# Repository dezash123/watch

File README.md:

ecad / code for my custom smartwatch!!!!!

[MCAD](https://cad.onshape.com/documents/7a2f9e69e051d257ea5e1b33/)

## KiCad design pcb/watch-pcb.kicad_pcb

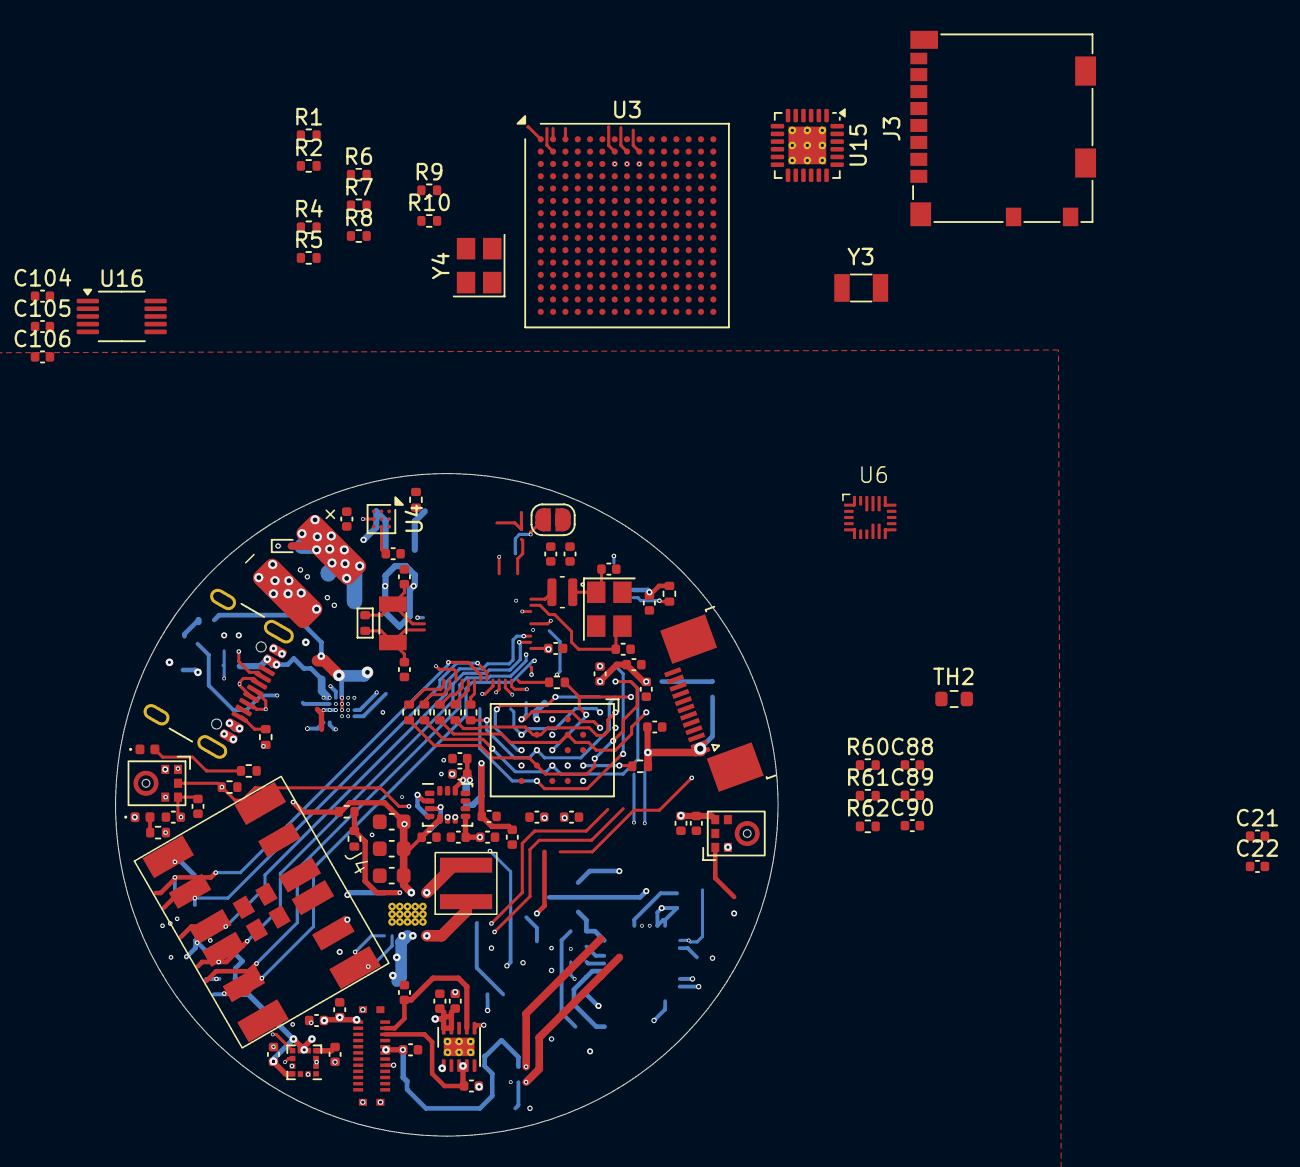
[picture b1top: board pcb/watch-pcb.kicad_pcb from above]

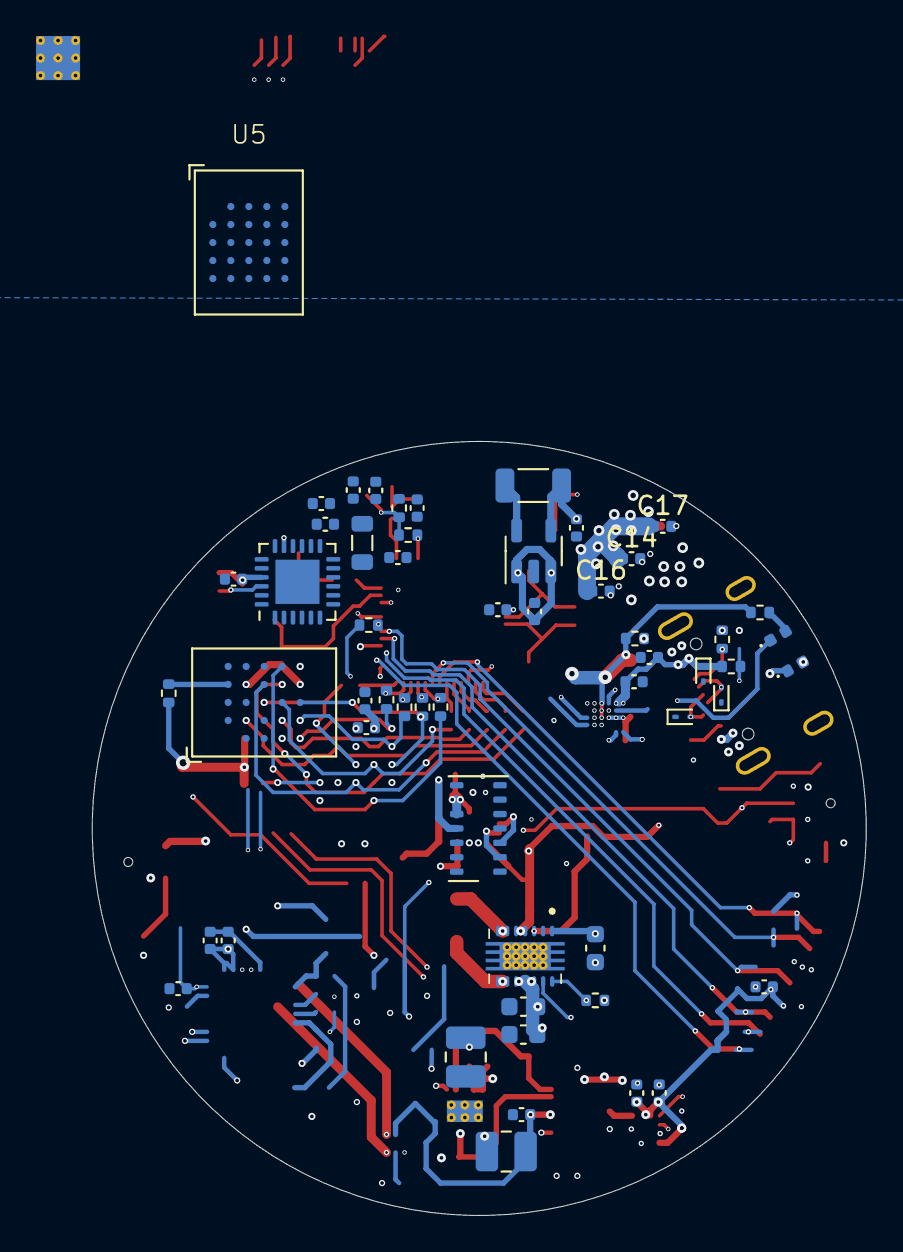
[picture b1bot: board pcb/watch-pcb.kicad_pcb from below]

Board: 6 copper layers, 43.0 x 43.0 mm, 158 parts (55 on the bottom side), 113 nets.

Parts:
BT1: Battery; Battery_Connector
C1, C2: 10uF; C_0603_1608Metric
C3, C58, C88: 4.7uF; C_0402_1005Metric
C4: 100nF; C_0603_1608Metric
C5, C36: 10nF; C_0402_1005Metric
C6, C13, C43, C44, C49, C52, C55, C62, C63, C89, C90: 10uF; C_0402_1005Metric
C7, C8, C10: 22uF; C_0603_1608Metric
C9, C11, C14, C18, C26, C31, C33, C40, C45, C47, C59, C64, C66, C69, C70, C75, C104, C106: 1uF; C_0402_1005Metric
C12, C17, C30, C32, C35, C38, C39, C46, C48, C50, C54, C57, C60, C61, C65, C67, C68, C71, C72, C73, C74, C76, C77, C78, C79, C105: 100nF; C_0402_1005Metric
C15: 2.2uF; C_0402_1005Metric
C16: 47nF; C_0402_1005Metric
C21, C22, C27, C28, C41, C42: C; C_0402_1005Metric
D1: STATUS1; LED_0402_1005Metric
D2, D3, D4, D5: ESD9B5.0ST5G; D_SOD-923
D6: CHARGING; LED_0402_1005Metric
D7: POWER GOOD; LED_0402_1005Metric
D15: STATUS0; LED_0402_1005Metric
J1: DAUGHTER; TE_1-1734839-2_1x12-1MP_P0.5mm_Horizontal
J2: USB_C_Receptacle; USB_C_Receptacle_GCT_USB4105-xx-A_16P_TopMnt_Horizontal
J3: Micro_SD_Card; microSD_HC_Molex_104031-0811
J4: ELV1411A
J6: TT143AMC12C; OK-14GF024-04
JP1: RESET=LOW; SolderJumper-2_P1.3mm_Open_RoundedPad1.0x1.5mm
L1: 1.5uH; XFL4020-152ME
L2: 1uH; L_1206_3216Metric
L5: 2nH; L_0805_2012Metric
L6: 24nH; L_Coilcraft_XFL2010
L7, L8: 10uH; L_1008_2520Metric
MK1, MK2: ICS-43434; InvenSense_ICS-43434-6_3.5x2.65mm
R1, R2, R4, R5, R6, R7, R8, R9, R10, R19, R31, R32, R40, R52, R53, R54: 10k; R_0402_1005Metric
R3, R39, R55, R56, R57: R; R_0402_1005Metric
R11, R12: 5.1k; R_0402_1005Metric
R13: 180k; R_0402_1005Metric
R14, R15: 1M; R_0402_1005Metric
R16: 22.1k; R_0402_1005Metric
R33: 499; R_0402_1005Metric
R34, R35, R36, R37, R38, R41, R42, R43, R44, R45: 0; R_0402_1005Metric
R60: 30.1; R_0402_1005Metric
R61: 5.32k; R_0402_1005Metric
R62: 5k; R_0402_1005Metric
TH2: 103AT-2 10k; R_0603_1608Metric
U1: ADP2108AUJ-1.8; TSOT-23-5
U2: TPS63021; Texas_VSON-14_3x4mm_ThermalPad
U3: STM32H7S7L8H6H; ST_TFBGA-225_13x13mm_Layout15x15_P0.8mm
U4: BQ27427YZFR; Texas_DSBGA-9_1.62mmx1.58mm_Layout3x3_P0.5mm
U5: APS256XXN-OBR-BG; BGA-24_6.0x8.0mm_Layout5x5_P1.0mm
U6: BQ25628E; Texas_WQFN-18_2.5x3.0mm_P0.4mm
U7: MX25LM51245GXDI00; BGA-24_6.0x8.0mm_Layout5x5_P1.0mm
U8: APS12808L-3OBMx; BGA-24_6.0x8.0mm_Layout5x5_P1.0mm
U9: TCA9535MRGER; VQFN-24-1EP_4x4mm_P0.5mm_EP2.45x2.45mm
U10: MAX30102; Maxim_OLGA-14_3.3x5.6mm_P0.8mm
U11: TPS65631W; WSON-10-1EP_2.5x2.5mm_P0.5mm_EP1.2x2mm_ThermalVias
U13: LSM6DSV16XTR; LGA-14_3x2.5mm_P0.5mm_LayoutBorder3x4y
U14: LIS3MDL; LGA-12_2x2mm_P0.5mm
U15: TXS02612RTW; WQFN-24-1EP_4x4mm_P0.5mm_EP2.45x2.45mm_ThermalVias
U16: DRV2605LDGS; VSSOP-10_3x3mm_P0.5mm
Y1, Y3: 32.768kHz; Crystal_SMD_3215-2Pin_3.2x1.5mm
Y2, Y4: 40MHz(10ppm); Crystal_SMD_3225-4Pin_3.2x2.5mm

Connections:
+1V8: C6.1, C54.2, C55.2, J1.3, J3.4 (VDD), L2.2, U1.4 (FB), U3.L8 (VDDXSPI_1), U3.L10 (VDDXSPI_1), U3.M8 (VDDXSPI_1), U3.M10 (VDDXSPI_1), U5.D1 (VDD_1), U5.E4 (VDD_2), U10.11 (VDD), U15.17 (VCC_{B1}), U15.21 (VCC_{B0})
+3V3: C7.2, C8.2, C10.2, C12.1, C13.2, C30.1, C31.1, C32.2, C33.2, C35.2, C36.2, C39.1, C40.1, C43.1, C44.1, C46.1, C47.1, C48.2, C49.1, C50.1, C52.2, C57.1, C58.1, C59.1, C60.1, C61.1, C64.1, C65.2, C66.1, C67.2, C68.2, C69.1, C70.2, C71.2, C72.2, C74.2, C75.1, C76.1, C77.1, C78.1, C79.1, C105.2, C106.1, J1.1, J1.2, J6.1 (VDD), J6.19 (IOVCC), J6.20 (VDD), L5.2, L8.1, MK1.5 (VDD), MK2.2 (LR), MK2.5 (VDD), R1.2, R2.2, R4.2, R5.2, R6.2, R7.2, R8.2, R9.2, R10.2, R14.2, R15.1, R31.2, R40.1, R52.1, R53.2, R56.2, R57.2, U2.4 (VOUT), U2.5 (VOUT), U3.C1 (VBAT), U3.F7 (VDD), U3.F9 (VDD), U3.F10 (VDD), U3.G6 (VDD), U3.H6 (VDD), U3.H10 (VDD), U3.H12 (VDDXSPI_2), U3.J11 (VDDXSPI_2), U3.K6 (VDD), U3.K8 (VDD), U3.K10 (VDD), U3.L9 (VDD), U7.B4 (VCC), U7.D1 (VCCQ), U7.E4 (VCCQ), U8.B4 (VDD), U8.D1 (VDDQ), U8.E4 (VDDQ), U9.21 (VCC), U10.9 (VLED+), U10.10 (VLED+), U11.9 (AVIN), U11.10 (PVIN), U13.5 (VDD_IO), U13.8 (VDD), U13.12 (CS), U14.5 (Vdd), U14.6 (Vdd_IO), U14.10 (~CS), U15.5 (V_{CCA}), U16.6 (VDD/NC), U16.10 (VDD)
+BATT: BT1.1 (+), C11.2, C90.1, D5.2 (A2), U4.C3 (BAT), U6.8 (BAT)
+VSW: C1.1, C2.2, C3.2, C4.2, U1.1 (Vin), U1.3 (EN), U2.1 (VINA), U2.10 (VIN), U2.11 (VIN), U2.12 (EN), U4.C2 (SRX), U6.9 (SYS)
/IO/AMOLED_N: C62.2, J6.23 (ELVSS), U11.7 (OUTN)
/IO/AMOLED_P: C63.2, J6.22 (ELVDD), U11.3 (OUTP), U11.4 (FBS)
/IO/IMU_SCL: U10.2 (SCL), U14.1 (SCL/SPC)
/IO/IMU_SDA: U10.3 (SDA), U14.11 (SDA/SDI/SDO)
/IO/MIC_SCK: MK1.4 (SCK), MK2.4 (SCK)
/IO/MIC_SD: MK1.6 (SD), MK2.6 (SD), R54.2
/IO/MIC_WS: MK1.1 (WS), MK2.1 (WS)
/IO/SI2C_SCL: J6.4 (SCL), U16.2 (SCL)
/IO/SI2C_SDA: J6.3 (SDA), U16.3 (SDA)
/IO/SWIRE: J6.17 (SWIRE), U11.6 (CTRL)
/MCU and Memory/CLK_N: C42.2, Y2.3
/MCU and Memory/EN: JP1.2 (B), R31.1, R32.1
/MCU and Memory/EXT_INT: R53.1, U9.22 (~INT)
/MCU and Memory/EXT_IO5: U2.13 (PS/SYNC), U9.7 (P06)
/MCU and Memory/EXT_IO7: J1.8, U9.10
/MCU and Memory/EXT_IO8: J1.9, U9.11
/MCU and Memory/EXT_IO9: J1.10, U9.12
/MCU and Memory/EXT_IO10: R55.2, U9.13
/MCU and Memory/EXT_IO11: R3.2, U9.14
/MCU and Memory/EXT_IO12: R1.1, U4.A1 (GPOUT), U9.15
/MCU and Memory/EXT_IO13: R2.1, U6.11 (INT), U9.16
/MCU and Memory/EXT_IO14: R15.2, U2.14 (PG), U9.17
/MCU and Memory/FLASH_RST: R40.2, U7.A4 (RESET#), U9.1 (P00)
/MCU and Memory/MEM_CLK: R36.1, U7.B2 (SCLK), U8.B2 (CLK)
/MCU and Memory/MEM_D0: R38.1, U7.D3 (SIO0), U8.D3 (ADQ0)
/MCU and Memory/MEM_D1: R37.1, U7.D2 (SIO1), U8.D2 (ADQ1)
/MCU and Memory/MEM_D2: R35.1, U7.C4 (SIO2), U8.C4 (ADQ2)
/MCU and Memory/MEM_D3: R34.1, U7.D4 (SIO3), U8.D4 (ADQ3)
/MCU and Memory/MEM_D4: R41.1, U7.D5 (SIO4), U8.D5 (ADQ4)
/MCU and Memory/MEM_D5: R42.1, U7.E3 (SIO5), U8.E3 (ADQ5)
/MCU and Memory/MEM_D6: R43.1, U7.E2 (SIO6), U8.E2 (ADQ6)
/MCU and Memory/MEM_D7: R44.1, U7.E1 (SIO7), U8.E1 (ADQ7)
/MCU and Memory/MEM_DQS: R45.1, U7.C3 (DQS), U8.C3 (DQS/DM)
/MCU and Memory/RAM_RST: R52.2, U8.A4 (RST#), U9.2 (P01)
/MCU and Memory/RTC_N: C28.2, R39.2, Y1.1
/MCU and Memory/RTC_P: C27.2, R39.1, Y1.2
/SI2C_SCL: J1.5, U4.A3 (SCL), U6.13 (SCL)
/SI2C_SDA: J1.4, U4.A2 (SDA), U6.12 (SDA)
/STM MCU/CLK_M: C22.2, U3.K2 (PH1-_OSC_OU_T), Y4.3
/STM MCU/CLK_P: C21.1, U3.K1 (PH0-_OSC_IN), Y4.1
/STM MCU/RAM_CLK: U3.R10 (PO4), U5.B2 (CLK)
/STM MCU/RAM_CS: U3.R13 (PO0), U5.A3 (CE#)
/STM MCU/RAM_D0: U3.P11 (PP0), U5.D3 (ADQ0)
/STM MCU/RAM_D1: U3.N12 (PP1), U5.D2 (ADQ1)
/STM MCU/RAM_D2: U3.N9 (PP2), U5.C4 (ADQ2)
/STM MCU/RAM_D3: U3.P9 (PP3), U5.D4 (ADQ3)
/STM MCU/RAM_D4: U3.R8 (PP4), U5.D5 (ADQ4)
/STM MCU/RAM_D5: U3.N10 (PP5), U5.E3 (ADQ5)
/STM MCU/RAM_D6: U3.R11 (PP6), U5.E2 (ADQ6)
/STM MCU/RAM_D7: U3.P12 (PP7), U5.E1 (ADQ7)
/STM MCU/RAM_D8: U3.P13 (PP8), U5.C2 (DQ8)
/STM MCU/RAM_D9: U3.R14 (PP9), U5.B1 (DQ9)
/STM MCU/RAM_D10: U3.M12 (PP10), U5.A2 (DQ10)
/STM MCU/RAM_D11: U3.P6 (PP11), U5.A4 (DQ11)
/STM MCU/RAM_D12: U3.N6 (PP12), U5.A5 (DQ12)
/STM MCU/RAM_D13: U3.R7 (PP13), U5.B4 (DQ13)
/STM MCU/RAM_D14: U3.N7 (PP14), U5.B5 (DQ14)
/STM MCU/RAM_D15: U3.P8 (PP15), U5.C5 (DQ15)
/STM MCU/RAM_DQS0: U3.N11 (PO2), U5.C3 (DQS/_DM0)
/STM MCU/RAM_DQS1: U3.M11 (PO3), U5.B3 (DQS/_DM1)
/STM MCU/RTC_CLK_M: U3.D1 (PC15-_OSC32_O_UT), Y3.1
/STM MCU/RTC_CLK_P: U3.D2 (PC14-_OSC32_I_N), Y3.2
/STM MCU/SD_DEV_CLK: J3.5 (CLK), U15.19 (CLK_{B0})
/STM MCU/SD_DEV_CMD: J3.3 (CMD), U15.20 (CMD_{B0})
/STM MCU/SD_DEV_D0: J3.7 (DAT0), U15.18 (DAT0_{B0})
/STM MCU/SD_DEV_D1: J3.8 (DAT1), U15.16 (DAT1_{B0})
/STM MCU/SD_DEV_D2: J3.1 (DAT2), U15.23 (DAT2_{B0})
/STM MCU/SD_DEV_D3: J3.2 (DAT3/CD), U15.22 (DAT3_{B0})
/STM MCU/SD_HOST_CLK: U3.D12 (PC12), U15.9 (CLKA)
/STM MCU/SD_HOST_CMD: U3.A14 (PD2), U15.4 (CMDA)
/STM MCU/SD_HOST_D0: U3.D15 (PC8), U15.6 (DAT0A)
/STM MCU/SD_HOST_D1: U3.E14 (PC9), U15.7 (DAT1A)
/STM MCU/SD_HOST_D2: U3.B14 (PC10), U15.1 (DAT2A)
/STM MCU/SD_HOST_D3: U3.B15 (PC11), U15.3 (DAT3A)
/USB and Power/ILIM: R62.1, U6.4 (ILIM)
/USB and Power/USB_DM: D4.2 (A2), J2.A7 (D-), J2.B7 (D-)
/USB and Power/USB_DP: D2.2 (A2), J2.A6 (D+), J2.B6 (D+)
GND: BT1.2 (-), C1.2, C2.1, C3.1, C4.1, C5.2, C6.2, C7.1, C8.1, C9.2, C10.1, C11.1, C14.2, C15.1, C17.2, C18.1, C21.2, C22.1, C26.2, C27.1, C28.1, C30.2, C31.2, C32.1, C33.1, C35.1, C36.1, C38.2, C39.2, C40.2, C41.2, C42.1, C43.2, C44.2, C45.2, C46.2, C47.2, C48.1, C49.2, C50.2, C52.1, C54.1, C55.1, C57.2, C58.2, C59.2, C60.2, C61.2, C62.1, C63.1, C64.2, C65.1, C66.2, C67.1, C68.1, C69.2, C70.1, C71.1, C72.1, C73.1, C74.1, C75.2, C76.2, C77.2, C78.2, C79.2, C88.2, C89.1, C90.2, C104.1, C105.1, C106.2, D1.1 (K), D2.1 (A1), D3.2 (A2), D4.1 (A1), D5.1 (A1), D15.1 (K), J1.11, J1.12, J2.A1 (GND), J2.A12 (GND), J2.B1 (GND), J2.B12 (GND), J3.6 (VSS), J3.9 (SHIELD), J6.6 (GND), J6.10 (GND), J6.12 (GND), J6.18 (GND), J6.24 (MTP_PWR), J6.25 (GND), JP1.1 (A), L7.1, MK1.2 (LR), MK1.3 (GND), MK2.3 (GND), R11.2, R12.2, R13.1, R19.1, R54.1, R60.1, R62.2, TH2.1, U1.2 (GND), U2.2 (GND), U2.15 (PGND), U3.A1 (VSS), U3.A8 (VSS), U3.A11 (VSS), U3.A15 (VSS), U3.D3 (VSS), U3.D6 (VSS), U3.E3 (VSS), U3.E8 (VSSUSB), U3.E9 (VSS), U3.F6 (VSS), U3.F15 (VSS), U3.G8 (VSS), U3.G10 (VSS), U3.G12 (VSS), U3.H2 (VSSSMP_S), U3.H7 (VSS), U3.H8 (VSS), U3.H9 (VSS), U3.H11 (VSS), U3.J1 (VSS), U3.J5 (VSSA), U3.J8 (VSS), U3.J10 (VSS), U3.J12 (VSS), U3.J15 (VSS), U3.K7 (VSS), U3.K9 (VSS), U3.L6 (VSS), U3.L11 (VSS), U3.M7 (VSS), U3.M9 (VSS), U3.M15 (VSS), U3.N8 (VSS), U3.R1 (VSS), U3.R6 (VSS), U3.R9 (VSS), U3.R12 (VSS), U3.R15 (VSS), U4.B2 (VSS), U4.C1 (VSS), U5.C1 (VSS_1), U5.E5 (VSS_2), U6.14 (CE), U6.15 (GND), U7.B3 (GND), U7.C1 (VSSQ), U7.E5 (VSSQ), U8.B3 (VSS), U8.C1 (VSSQ), U8.E5 (VSSQ), U9.9 (GND), U9.18 (A0), U9.23 (A1), U9.24 (A2), U9.25 (EPAD), U10.4 (PGND), U10.12 (GND), U11.2 (PGND), U11.5 (AGND), U11.11 (GND), U13.1 (SDO/SA0), U13.6 (GND), U13.7 (GND), U14.2 (GND), U14.3 (GND), U14.9 (SDO/SA1), U14.12 (GND), U15.2 (GND), U15.11 (GND), U15.24 (SEL), U15.25 (EPAD), U16.4 (IN/TRIG), U16.8 (GND), Y2.2, Y2.4, Y4.2, Y4.4
unnamed: C26.1, R32.2
unnamed: C38.1, L5.1
unnamed: C41.1, L6.1, Y2.1
unnamed: D1.2 (A), R3.1
unnamed: D6.2 (A), R56.1
unnamed: D6.1 (K), U6.10 (STAT)
unnamed: D7.2 (A), R57.1
unnamed: D7.1 (K), U6.3 (PG)
unnamed: D15.2 (A), R55.1
unnamed: J2.A5 (CC1), R11.1
unnamed: J2.B5 (CC2), R12.1
unnamed: L1.1, U2.8 (L1), U2.9 (L1)
unnamed: L1.2, U2.6 (L2), U2.7 (L2)
unnamed: C9.1, R16.1
unnamed: C12.2, C13.1
unnamed: L2.1, U1.5 (SW)
unnamed: R13.2, R14.1, U2.3 (FB)
unnamed: C45.1, U3.A6 (BOOT0)
unnamed: R19.2, U4.B1 (BIN)
unnamed: C15.2, U4.B3 (VDD)
unnamed: C16.1, U6.1 (BTST)
unnamed: C17.1, C89.2, U6.17 (PMID)
unnamed: C88.1, U6.2 (REGN)
unnamed: C16.2, U6.16 (SW)
unnamed: R60.2, R61.1, TH2.2, U6.6 (TS)
unnamed: R61.2, U6.5 (TS_BIAS)
unnamed: L7.2, U11.8 (SWN)
unnamed: L8.2, U11.1 (SWP)
unnamed: C73.2, U14.4 (C1)
unnamed: C104.2, U16.1 (REG)
VBUS: C5.1, C14.1, C18.2, D3.1 (A1), J2.A4 (VBUS), J2.A9 (VBUS), J2.B4 (VBUS), J2.B9 (VBUS), R16.2, U6.18 (VBUS)

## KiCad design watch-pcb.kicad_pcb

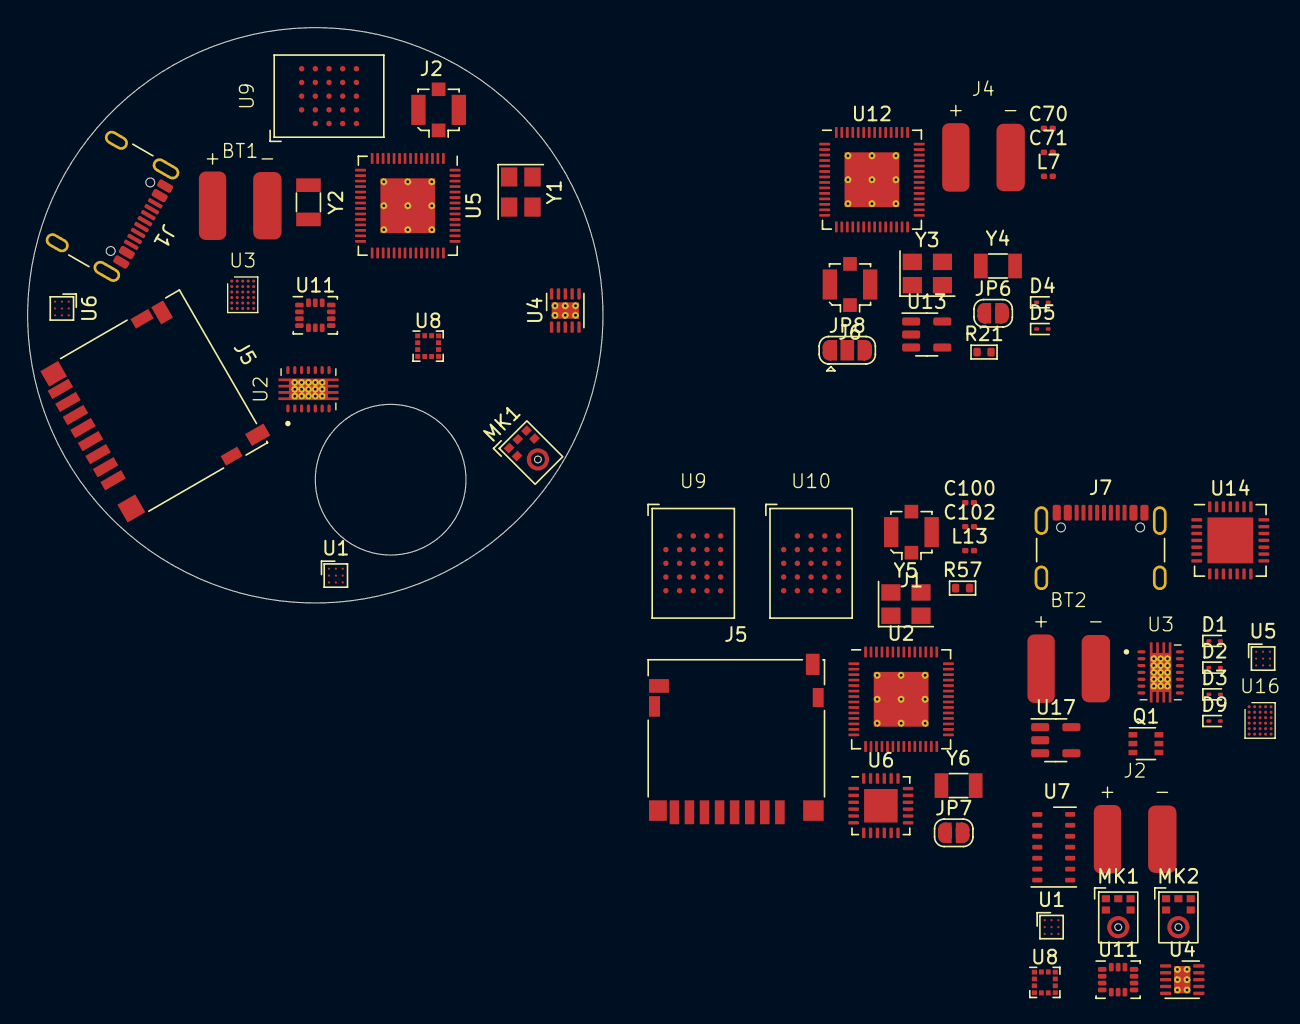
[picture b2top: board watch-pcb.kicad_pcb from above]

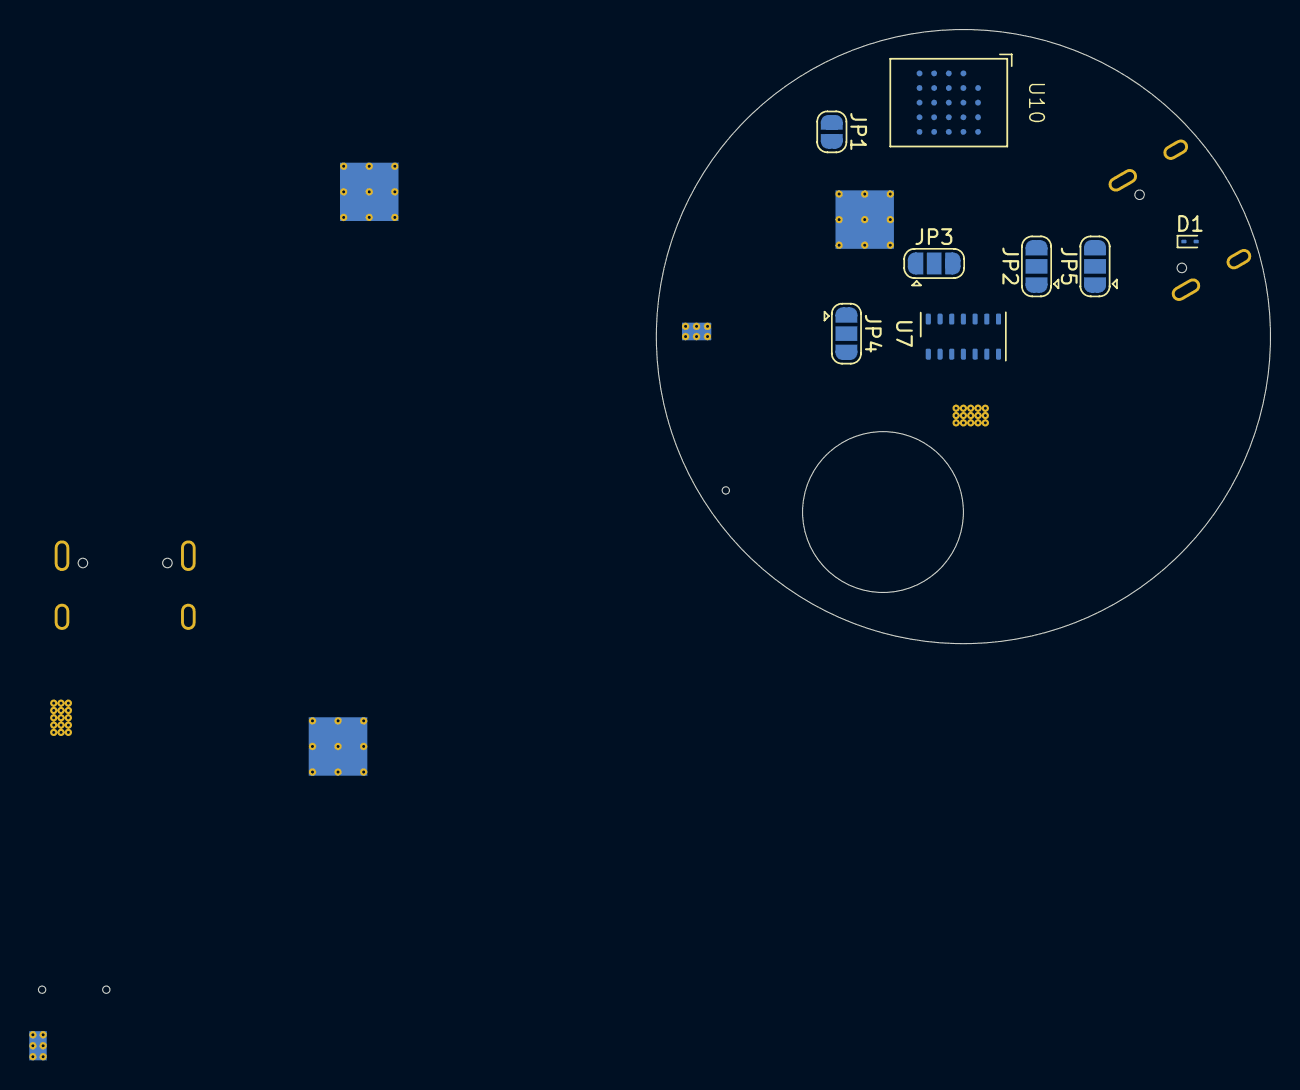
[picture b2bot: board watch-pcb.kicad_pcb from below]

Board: 4 copper layers, 42.0 x 42.0 mm, 71 parts (8 on the bottom side), 128 nets, no tracks yet.

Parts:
BT1, BT2: Battery; Battery_Connector
C70, C71, C100, C102: 1.5pF; C_0201_0603Metric
D1, D1#2, D2, D3, D9: ESD9B5.0ST5G; D_SOD-923
D4, D5: ESD9B3.3ST5G; D_SOD-923
J1, J7: USB_C_Receptacle; USB_C_Receptacle_GCT_USB4105-xx-A_16P_TopMnt_Horizontal
J1#2, J2#2, J6: ESP_ANT; U.FL_Molex_MCRF_73412-0110_Vertical
J2, J4: MOTOR; Battery_Connector
J5, J5#2: Micro_SD_Card; microSD_HC_Hirose_DM3D-SF
JP1: BOOT; SolderJumper-2_P1.3mm_Open_RoundedPad1.0x1.5mm
JP2, JP3, JP4, JP5, JP8: GP6; SolderJumper-3_P1.3mm_Open_RoundedPad1.0x1.5mm
JP6, JP7: RESET=LOW; SolderJumper-2_P1.3mm_Open_RoundedPad1.0x1.5mm
L7, L13: 2.7nH; L_0201_0603Metric
MK1, MK1#2, MK2: ICS-43434; InvenSense_ICS-43434-6_3.5x2.65mm
Q1: MBT2222ADW1T1; SOT-363_SC-70-6
R21, R57: R; R_0402_1005Metric
U1, U1#2: DRV2605LYZFR; Texas_DSBGA-9_1.4715x1.4715mm_Layout3x3_P0.5mm
U2, U3: TPS63021; Texas_VSON-14_3x4mm_ThermalPad
U2#2, U5#2, U12: ESP32-S3; QFN-56-1EP_7x7mm_P0.4mm_EP4x4mm_ThermalVias
U3#2, U16: BQ25638; Texas_DSBGA-30_2.0x2.4mm_Layout5x6_P0.4mm
U4, U4#2: TPS65631W; WSON-10-1EP_2.5x2.5mm_P0.5mm_EP1.2x2mm_ThermalVias
U5, U6: BQ27427YZFR; Texas_DSBGA-9_1.4715x1.4715mm_Layout3x3_P0.5mm
U6#2: TCA9535MRGER; VQFN-24-1EP_4x4mm_P0.5mm_EP2.45x2.45mm
U7, U7#2: MAX30102; Maxim_OLGA-14_3.3x5.6mm_P0.8mm
U8, U8#2: LIS3MDL; LGA-12_2x2mm_P0.5mm
U9, U9#2: MX25LM51245GXDI00; BGA-24_6.0x8.0mm_Layout5x5_P1.0mm
U10, U10#2: APS12808L-3OBMx; BGA-24_6.0x8.0mm_Layout5x5_P1.0mm
U11, U11#2: LSM6DSV16XTR; LGA-14_3x2.5mm_P0.5mm_LayoutBorder3x4y
U13, U17: ADP2108AUJ-1.8; TSOT-23-5
U14: CP2102N-Axx-xQFN28; QFN-28-1EP_5x5mm_P0.5mm_EP3.35x3.35mm
Y1, Y3, Y5: 40MHz(10ppm); Crystal_SMD_3225-4Pin_3.2x2.5mm
Y2, Y4, Y6: 32.768kHz; Crystal_SMD_3215-2Pin_3.2x1.5mm

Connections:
+1V8: U5#2.29 (VDD_SPI), U7.11 (VDD), U7#2.11 (VDD), U13.4 (FB), U17.4 (FB)
+3V3: J5.4 (VDD), J5#2.4 (VDD), MK1.2 (LR), MK1.5 (VDD), MK1#2.5 (VDD), MK2.5 (VDD), U1.C2 (VDD), U1#2.A1 (EN), U1#2.C2 (VDD), U2.4 (VOUT), U2.5 (VOUT), U2#2.55 (VDDA1), U2#2.56 (VDDA2), U3.4 (VOUT), U3.5 (VOUT), U4.9 (AVIN), U4.10 (PVIN), U4#2.9 (AVIN), U4#2.10 (PVIN), U5.C2 (SRX), U5#2.20 (VDD3P3_RTC), U5#2.46 (VDD3P3_CPU), U5#2.55 (VDDA1), U5#2.56 (VDDA2), U6.C2 (SRX), U6#2.21 (VCC), U7.9 (VLED+), U7.10 (VLED+), U7#2.9 (VLED+), U7#2.10 (VLED+), U8.5 (Vdd), U8.6 (Vdd_IO), U8.10 (~CS), U8#2.5 (Vdd), U8#2.6 (Vdd_IO), U8#2.10 (~CS), U9.B4 (VCC), U9.D1 (VCCQ), U9.E4 (VCCQ), U9#2.B4 (VCC), U9#2.D1 (VCCQ), U9#2.E4 (VCCQ), U10.B4 (VDD), U10.D1 (VDDQ), U10.E4 (VDDQ), U10#2.B4 (VDD), U10#2.D1 (VDDQ), U10#2.E4 (VDDQ), U11.5 (VDD_IO), U11.8 (VDD), U11.12 (CS), U11#2.5 (VDD_IO), U11#2.8 (VDD), U11#2.12 (CS), U12.55 (VDDA1), U12.56 (VDDA2), U14.6 (VDD), U14.7 (VREGIN)
+5V: D1#2.1 (A1), J1.A4 (VBUS), J1.A9 (VBUS), J1.B4 (VBUS), J1.B9 (VBUS), U3#2.A1 (VBUS), U3#2.B1 (VBUS)
+BATT: BT2.1 (+), D1.2 (A2), U5.C3 (BAT), U16.E1 (BAT), U16.E2 (BAT), U16.E3 (BAT), U16.F1 (BATP)
+VSW: U3.1 (VINA), U3.10 (VIN), U3.11 (VIN), U3.12 (EN), U16.D1 (SYS), U16.D2 (SYS), U16.D3 (SYS), U17.1 (Vin), U17.3 (EN)
/AMOLED_P: U4.3 (OUTP), U4.4 (FBS)
/BAT+: BT1.1 (+), U3#2.E1 (BAT), U3#2.E2 (BAT), U3#2.E3 (BAT), U3#2.F1 (BATP), U6.C3 (BAT)
/BAT_LOW: U5#2.10 (GPIO5), U6.A1 (GPOUT)
/BTN1: U5#2.37 (SPICLK_P), U12.51 (GPIO45)
/CHG_INT: U3#2.F5 (INT), U5#2.9 (GPIO4)
/CLK_N: U5#2.53 (XTAL_N), U12.53 (XTAL_N), Y1.3, Y3.3
/CLK_P: U5#2.54 (XTAL_P), U12.54 (XTAL_P), Y1.1, Y3.1
/DISP_RST: JP4.1 (A), JP8.1 (A)
/ESP_ANT: C71.1, L7.2, U5#2.1 (LNA_IN), U12.1 (LNA_IN)
/GP6: JP2.2 (C), U5#2.11 (GPIO6)
/GP18: JP5.2 (C), U5#2.24 (GPIO18)
/GP21: JP3.2 (C), U5#2.27 (GPIO21)
/GP45: JP4.2 (C), JP8.2 (C), U5#2.51 (GPIO45)
/HBT_INT: JP4.3 (B), JP8.3 (B), U7#2.13 (~INT)
/I2C0_SCL: JP1.2 (B), U1#2.C1 (SCL), U3#2.D5 (SCL), U5#2.5 (GPIO0), U6.A3 (SCL), U12.5 (GPIO0)
/I2C0_SDA: U1#2.B2 (SDA), U3#2.E5 (SDA), U5#2.6 (GPIO1), U6.A2 (SDA), U12.6 (GPIO1)
/I2C1_SCL: U5#2.7 (GPIO2), U11#2.13 (SCL), U12.7 (GPIO2)
/I2C1_SDA: U5#2.8 (GPIO3), U11#2.14 (SDA), U12.8 (GPIO3)
/IMU_SCL: U7#2.2 (SCL), U8.1 (SCL/SPC), U11#2.3 (SCx/AH2/QVAR2)
/IMU_SDA: U7#2.3 (SDA), U8.11 (SDA/SDI/SDO), U11#2.2 (SDx/AH1/QVAR1)
/IMU_Wakeup: U5#2.23 (GPIO17), U11#2.4 (INT1)
/IO/AMOLED_P: U4#2.3 (OUTP), U4#2.4 (FBS)
/IO/FI2C_SCL: U2#2.7 (GPIO2), U11.13 (SCL)
/IO/FI2C_SDA: U2#2.8 (GPIO3), U11.14 (SDA)
/IO/HBT_INT: U6#2.4 (P03), U7.13 (~INT)
/IO/IMU_INT1: U2#2.13 (GPIO8), U11.4 (INT1)
/IO/IMU_INT2: U2#2.23 (GPIO17), U11.9 (INT2)
/IO/IMU_SCL: U7.2 (SCL), U8#2.1 (SCL/SPC), U11.3 (SCx/AH2/QVAR2)
/IO/IMU_SDA: U7.3 (SDA), U8#2.11 (SDA/SDI/SDO), U11.2 (SDx/AH1/QVAR1)
/IO/MAG_DRDY: U6#2.3 (P02), U8#2.8 (DRDY)
/IO/MAG_INT: U6#2.6 (P05), U8#2.7 (INT)
/IO/MIC_SCK: MK1.4 (SCK), MK2.4 (SCK), U2#2.51 (GPIO45)
/IO/MIC_SD: MK1.6 (SD), MK2.6 (SD), U2#2.43 (GPIO38)
/IO/MIC_WS: MK1.1 (WS), MK2.1 (WS), U2#2.52 (GPIO46)
/IO/MTR_EN: U1.A1 (EN), U6#2.5 (P04)
/MAG_INT: JP3.1 (A), U8.7 (INT)
/MCU and Memory/CLK_N: U2#2.53 (XTAL_N), Y5.3
/MCU and Memory/ECS: U2#2.27 (GPIO21), U9.A5 (ECS#)
/MCU and Memory/ESP_ANT: C102.1, L13.2, U2#2.1 (LNA_IN)
/MCU and Memory/EXT_INT: U2#2.26 (GPIO20), U6#2.22 (~INT)
/MCU and Memory/EXT_IO5: U3.13 (PS/SYNC), U6#2.7 (P06)
/MCU and Memory/EXT_IO12: U5.A1 (GPOUT), U6#2.15
/MCU and Memory/EXT_IO13: U6#2.16, U16.F5 (INT)
/MCU and Memory/EXT_IO14: U3.14 (PG), U6#2.17
/MCU and Memory/FLASH_RST: U6#2.1 (P00), U9.A4 (RESET#)
/MCU and Memory/MEM_CLK: U9.B2 (SCLK), U10.B2 (CLK)
/MCU and Memory/MEM_CS0: U2#2.32 (SPICS0), U9.C2 (CS#)
/MCU and Memory/MEM_CS1: U2#2.28 (SPICS1), U10.A3 (CE#)
/MCU and Memory/MEM_D0: U9.D3 (SIO0), U10.D3 (ADQ0)
/MCU and Memory/MEM_D1: U9.D2 (SIO1), U10.D2 (ADQ1)
/MCU and Memory/MEM_D2: U9.C4 (SIO2), U10.C4 (ADQ2)
/MCU and Memory/MEM_D3: U9.D4 (SIO3), U10.D4 (ADQ3)
/MCU and Memory/MEM_D4: U9.D5 (SIO4), U10.D5 (ADQ4)
/MCU and Memory/MEM_D5: U9.E3 (SIO5), U10.E3 (ADQ5)
/MCU and Memory/MEM_D6: U9.E2 (SIO6), U10.E2 (ADQ6)
/MCU and Memory/MEM_D7: U9.E1 (SIO7), U10.E1 (ADQ7)
/MCU and Memory/MEM_DQS: U9.C3 (DQS), U10.C3 (DQS/DM)
/MCU and Memory/RAM_RST: U6#2.2 (P01), U10.A4 (RST#)
/MCU and Memory/RTC_N: R57.2, U2#2.22 (XTAL_32K_N), Y6.1
/MCU and Memory/RTC_P: R57.1, U2#2.21 (XTAL_32K_P), Y6.2
/MCU and Memory/SD_CLK: J5#2.5 (CLK), U2#2.36 (SPICLK_N)
/MCU and Memory/SD_CMD: J5#2.3 (CMD), U2#2.37 (SPICLK_P)
/MCU and Memory/SD_D0: J5#2.7 (DAT0), U2#2.44 (MTCK)
/MCU and Memory/SD_D1: J5#2.8 (DAT1), U2#2.45 (MTDO)
/MCU and Memory/SD_D2: J5#2.1 (DAT2), U2#2.47 (MTDI)
/MCU and Memory/SD_D3: J5#2.2 (DAT3/CD), U2#2.48 (MTMS)
/MEM_CLK: U9#2.B2 (SCLK), U10#2.B2 (CLK)
/MEM_CS0: U5#2.32 (SPICS0), U9#2.C2 (CS#)
/MEM_CS1: U5#2.28 (SPICS1), U10#2.A3 (CE#)
/MEM_D0: U9#2.D3 (SIO0), U10#2.D3 (ADQ0)
/MEM_D1: U9#2.D2 (SIO1), U10#2.D2 (ADQ1)
/MEM_D2: U9#2.C4 (SIO2), U10#2.C4 (ADQ2)
/MEM_D3: U9#2.D4 (SIO3), U10#2.D4 (ADQ3)
/MEM_D4: U9#2.D5 (SIO4), U10#2.D5 (ADQ4)
/MEM_D5: U9#2.E3 (SIO5), U10#2.E3 (ADQ5)
/MEM_D6: U9#2.E2 (SIO6), U10#2.E2 (ADQ6)
/MEM_D7: U9#2.E1 (SIO7), U10#2.E1 (ADQ7)
/MEM_DQS: U9#2.C3 (DQS), U10#2.C3 (DQS/DM)
/MIC_SCK: MK1#2.4 (SCK), U5#2.43 (GPIO38)
/MIC_SD: MK1#2.6 (SD), U5#2.52 (GPIO46)
/MIC_WS: MK1#2.1 (WS), U5#2.12 (GPIO7)
/MTR_M: J4.2, U1#2.C3 (OUT-)
/MTR_P: J4.1, U1#2.A3 (OUT+)
/PWR: U2#2.25 (GPIO19), U16.D4 (QON)
/RTC_N: R21.2, U5#2.22 (XTAL_32K_N), U12.22 (XTAL_32K_N), Y2.1, Y4.1
/RTC_P: R21.1, U5#2.21 (XTAL_32K_P), U12.21 (XTAL_32K_P), Y2.2, Y4.2
/SD_CLK: J5.5 (CLK), U5#2.49 (U0TXD), U12.49 (U0TXD)
/SD_CMD: J5.3 (CMD), U5#2.50 (U0RXD), U12.50 (U0RXD)
/SD_D0: J5.7 (DAT0), U5#2.44 (MTCK), U12.44 (MTCK)
/SD_D1: J5.8 (DAT1), U5#2.45 (MTDO), U12.45 (MTDO)
/SD_D2: J5.1 (DAT2), U5#2.47 (MTDI), U12.47 (MTDI)
/SD_D3: J5.2 (DAT3/CD), U5#2.48 (MTMS), U12.48 (MTMS)
/SI2C_SCL: U1.C1 (SCL), U2#2.5 (GPIO0), U5.A3 (SCL), U6#2.20 (SDA), U16.D5 (SCL)
/SI2C_SDA: U1.B2 (SDA), U2#2.6 (GPIO1), U5.A2 (SDA), U6#2.19 (SCL), U16.E5 (SDA)
/USB and Power/DTR: Q1.4 (E2), U14.28 (~DTR)
/USB and Power/RTS: Q1.1 (E1), U14.24 (~RTS)
/USB and Power/USB_DM: D9.2 (A2), J7.A7 (D-), J7.B7 (D-), U14.5 (D-)
/USB and Power/USB_DP: D2.2 (A2), J7.A6 (D+), J7.B6 (D+), U14.4 (D+)
/USB_DM: D5.2 (A2), J1.A7 (D-), J1.B7 (D-), U5#2.25 (GPIO19), U12.25 (GPIO19)
/USB_DP: D4.2 (A2), J1.A6 (D+), J1.B6 (D+), U5#2.26 (GPIO20), U12.26 (GPIO20)
GND: BT1.2 (-), BT2.2 (-), C70.2, C71.2, C100.2, C102.2, D1.1 (A1), D1#2.2 (A2), D2.1 (A1), D3.2 (A2), D4.1 (A1), D5.1 (A1), D9.1 (A1), J1.A1 (GND), J1.A12 (GND), J1.B1 (GND), J1.B12 (GND), J1.S1 (SHIELD), J1#2.2 (Ext), J2#2.2 (Ext), J5.6 (VSS), J5.9 (SHIELD), J5#2.6 (VSS), J5#2.9 (SHIELD), J6.2 (Ext), J7.A1 (GND), J7.A12 (GND), J7.B1 (GND), J7.B12 (GND), JP1.1 (A), JP6.1 (A), JP7.1 (A), MK1.3 (GND), MK1#2.2 (LR), MK1#2.3 (GND), MK2.2 (LR), MK2.3 (GND), U1.B1 (IN/TRIG), U1.B3 (GND), U1#2.B1 (IN/TRIG), U1#2.B3 (GND), U2.2 (GND), U2.15 (PGND), U2#2.57 (GND), U3.2 (GND), U3.15 (PGND), U3#2.A4 (PGND), U3#2.B4 (PGND), U3#2.C4 (PGND), U3#2.C5 (ADCIN), U3#2.F2 (CE), U4.2 (PGND), U4.5 (AGND), U4.11 (GND), U4#2.2 (PGND), U4#2.5 (AGND), U4#2.11 (GND), U5.B2 (VSS), U5.C1 (VSS), U5#2.57 (GND), U6.B2 (VSS), U6.C1 (VSS), U6#2.9 (GND), U6#2.18 (A0), U6#2.23 (A1), U6#2.24 (A2), U6#2.25 (EPAD), U7.4 (PGND), U7.12 (GND), U7#2.4 (PGND), U7#2.12 (GND), U8.2 (GND), U8.3 (GND), U8.9 (SDO/SA1), U8.12 (GND), U8#2.2 (GND), U8#2.3 (GND), U8#2.9 (SDO/SA1), U8#2.12 (GND), U9.B3 (GND), U9.C1 (VSSQ), U9.E5 (VSSQ), U9#2.B3 (GND), U9#2.C1 (VSSQ), U9#2.E5 (VSSQ), U10.B3 (VSS), U10.C1 (VSSQ), U10.E5 (VSSQ), U10#2.B3 (VSS), U10#2.C1 (VSSQ), U10#2.E5 (VSSQ), U11.1 (SDO/SA0), U11.6 (GND), U11.7 (GND), U11#2.1 (SDO/SA0), U11#2.6 (GND), U11#2.7 (GND), U12.57 (GND), U13.2 (GND), U14.3 (GND), U14.29 (GND), U16.A4 (PGND), U16.B4 (PGND), U16.C4 (PGND), U16.C5 (ADCIN), U16.F2 (CE), U17.2 (GND), Y1.2, Y1.4, Y3.2, Y3.4, Y5.2, Y5.4
unnamed: U3#2.A2 (PMID), U3#2.B2 (PMID)
unnamed: U3#2.A3 (SW), U3#2.B3 (SW), U3#2.C3 (SW)
unnamed: U16.A2 (PMID), U16.B2 (PMID)
unnamed: U16.A3 (SW), U16.B3 (SW), U16.C3 (SW)
unnamed: C100.1, J1#2.1 (In), L13.1
unnamed: J2.1, U1.A3 (OUT+)
unnamed: J2.2, U1.C3 (OUT-)
unnamed: C70.1, J6.1 (In), L7.1
unnamed: U2.8 (L1), U2.9 (L1)
unnamed: U2.6 (L2), U2.7 (L2)
unnamed: U3.8 (L1), U3.9 (L1)
unnamed: U3.6 (L2), U3.7 (L2)
unnamed: U1.A2 (REG), U1#2.A2 (REG)
unnamed: U2#2.2 (VDD3P3), U2#2.3 (VDD3P3__1)
unnamed: U2#2.20 (VDD3P3_RTC), U2#2.46 (VDD3P3_CPU)
unnamed: U4.8 (SWN), U4#2.8 (SWN)
unnamed: U4.1 (SWP), U4#2.1 (SWP)
unnamed: U5#2.2 (VDD3P3), U5#2.3 (VDD3P3__1)
unnamed: U8.4 (C1), U8#2.4 (C1)
unnamed: U12.2 (VDD3P3), U12.3 (VDD3P3__1)
unnamed: U12.20 (VDD3P3_RTC), U12.46 (VDD3P3_CPU)
VBUS: D3.1 (A1), J7.A4 (VBUS), J7.A9 (VBUS), J7.B4 (VBUS), J7.B9 (VBUS), U2.1 (VINA), U2.10 (VIN), U2.11 (VIN), U2.12 (EN), U2.13 (PS/SYNC), U3#2.D1 (SYS), U3#2.D2 (SYS), U3#2.D3 (SYS), U13.1 (Vin), U13.3 (EN), U16.A1 (VBUS), U16.B1 (VBUS)
